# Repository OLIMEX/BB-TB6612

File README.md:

# BB-TB6612
Dual DC motor driver board for motors up to 12V 1.2A

Product page: https://www.olimex.com/Products/Robot-CNC-Parts/MotorDrivers/BB-TB6612/

## Licensee
* Hardware is released under CERN Open Hardware Licence Version 2 -
Strongly Reciprocal
* Software is released under GPL3 Licensee
* Documentation is released under CC BY-SA 3.0

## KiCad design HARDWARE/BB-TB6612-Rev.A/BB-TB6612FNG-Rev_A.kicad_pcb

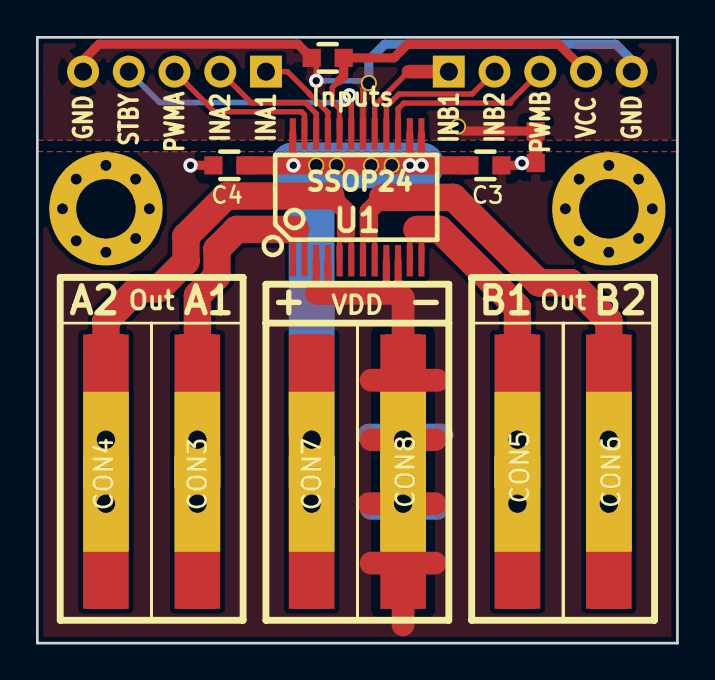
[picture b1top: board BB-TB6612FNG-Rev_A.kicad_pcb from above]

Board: 2 copper layers, 35.6 x 33.7 mm, 21 parts (0 on the bottom side), 15 nets.

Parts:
C2, C3, C4: 10uF/25V; C_0603_5MIL_DWS
CON1: INA; HN1x5
CON2: INB; HN1x5
CON3: AO1; N1_SMD
CON4: AO2; N1_SMD
CON5: BO1; N1_SMD
CON6: BO2; N1_SMD
CON7: VDD; N1_SMD
CON8: PGND; N1_SMD
MountingHoleShield**: Mounting_hole_Shield_3.3mm
MountingHoleShield**#2: Mounting_hole_Shield_3.3mm
R1: 0R; R_0603_5MIL_0R(Board_Mounted)
Ref**: Val**; via_09_07
Ref**#2, Ref**#3, Ref**#4, Ref**#5, Ref**#6: Val**; via_09_07
U1: TB6612FNG; SSOP24

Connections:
/AIN1: CON1.1, U1.21
/AIN2: CON1.2, U1.22
/AO1: CON3.1, U1.1, U1.2
/AO2: CON4.1, U1.5, U1.6
/BIN1: CON2.1, U1.17
/BIN2: CON2.2, U1.16
/BO1: CON5.1, U1.11, U1.12
/BO2: CON6.1, U1.7, U1.8
/GND: C2.2, CON1.5, CON2.5, R1.1, Ref**.0, Ref**#2.0, U1.18
/PGND: C3.2, C4.2, CON8.1, R1.2, U1.3, U1.4, U1.9, U1.10
/PWMA: CON1.3, U1.23
/PWMB: CON2.3, U1.15
/STBY: CON1.4, U1.19
/VCC: C2.1, CON2.4, U1.20
/VDD: C3.1, C4.1, CON7.1, Ref**#3.0, Ref**#4.0, Ref**#5.0, Ref**#6.0, U1.13, U1.14, U1.24

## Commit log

2020-05-18 initial upload
